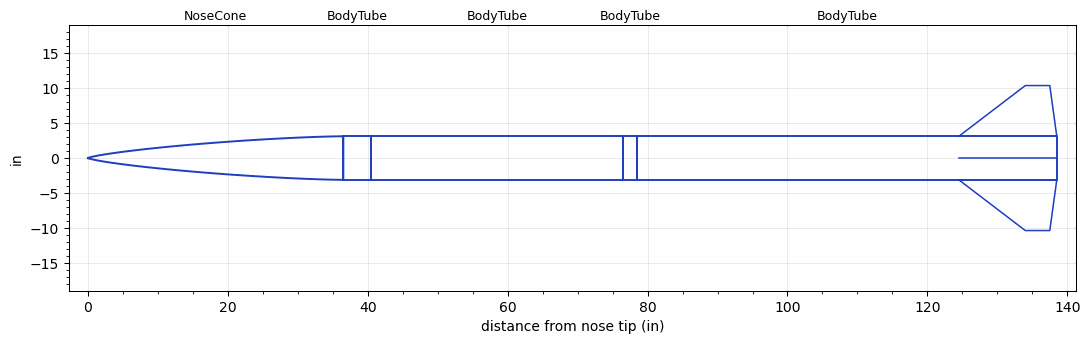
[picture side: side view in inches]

<RASAeroDocument>
 <FileVersion>2</FileVersion>
 <RocketDesign>
  <NoseCone>
   <Length>36.5</Length>
   <Diameter>6.23</Diameter>
   <Shape>Von Karman Ogive</Shape>
   <BluntRadius>0.075</BluntRadius>
   <Location>0</Location>
  </NoseCone>
  <BodyTube>
   <Length>4</Length>
   <Diameter>6.23</Diameter>
   <Location>36.5</Location>
  </BodyTube>
  <BodyTube>
   <Length>36</Length>
   <Diameter>6.23</Diameter>
   <Location>40.5</Location>
  </BodyTube>
  <BodyTube>
   <Length>2</Length>
   <Diameter>6.23</Diameter>
   <Location>76.5</Location>
  </BodyTube>
  <BodyTube>
   <Length>60</Length>
   <Diameter>6.23</Diameter>
   <Location>78.5</Location>
   <Fin>
    <Count>4</Count>
    <Chord>14</Chord>
    <Span>7.25</Span>
    <SweepDistance>9.5</SweepDistance>
    <TipChord>3.5</TipChord>
    <Thickness>0.375</Thickness>
    <LERadius>0.075</LERadius>
    <Location>14</Location>
    <AirfoilSection>Hexagonal</AirfoilSection>
    <FX1>1</FX1>
    <FX3>1</FX3>
   </Fin>
  </BodyTube>
  <Surface>Smooth Paint</Surface>
  <ModifiedBarrowman>False</ModifiedBarrowman>
  <Turbulence>False</Turbulence>
  <UseBooster1>False</UseBooster1>
  <UseBooster2>False</UseBooster2>
  <Comments>Includes new fin geometry to remove tip rake angle to allow for more accurate RasAero simluation verification</Comments>
 </RocketDesign>
 <LaunchSite>
  <Altitude>4596</Altitude>
  <Pressure>25.28</Pressure>
  <RodAngle>4</RodAngle>
  <RodLength>17</RodLength>
  <Temperature>95</Temperature>
  <WindSpeed>7</WindSpeed>
 </LaunchSite>
 <Recovery>
  <Altitude1>1500</Altitude1>
  <Altitude2>1500</Altitude2>
  <DeviceType1>Parachute</DeviceType1>
  <DeviceType2>Parachute</DeviceType2>
  <Event1>True</Event1>
  <Event2>True</Event2>
  <Size1>119.9998</Size1>
  <Size2>24</Size2>
  <EventType1>Altitude</EventType1>
  <EventType2>Altitude</EventType2>
  <CD1>1.16</CD1>
  <CD2>0</CD2>
 </Recovery>
 <SimulationList>
  <Simulation>
   <SustainerEngine>O4176  (EX)</SustainerEngine>
   <SustainerLaunchWt>139</SustainerLaunchWt>
   <SustainerNozzleDiameter>2</SustainerNozzleDiameter>
   <SustainerCG>95.03</SustainerCG>
   <SustainerIgnitionDelay>0</SustainerIgnitionDelay>
   <Booster1SeparationDelay>0</Booster1SeparationDelay>
   <Booster1IgnitionDelay>0</Booster1IgnitionDelay>
   <IncludeBooster1>False</IncludeBooster1>
   <Booster2Delay>0</Booster2Delay>
   <IncludeBooster2>False</IncludeBooster2>
   <TimetoApogee>51.82731</TimetoApogee>
   <MaxAltitude>41473.37</MaxAltitude>
   <MaxVelocity>1918.314</MaxVelocity>
  </Simulation>
  <Simulation>
   <SustainerLaunchWt>138.5684</SustainerLaunchWt>
   <SustainerCG>94.979</SustainerCG>
   <SustainerIgnitionDelay>0</SustainerIgnitionDelay>
   <Booster1SeparationDelay>0</Booster1SeparationDelay>
   <Booster1IgnitionDelay>0</Booster1IgnitionDelay>
   <IncludeBooster1>False</IncludeBooster1>
   <Booster2Delay>0</Booster2Delay>
   <IncludeBooster2>False</IncludeBooster2>
  </Simulation>
  <Simulation>
   <SustainerLaunchWt>138.5684</SustainerLaunchWt>
   <SustainerCG>94.979</SustainerCG>
   <SustainerIgnitionDelay>0</SustainerIgnitionDelay>
   <Booster1SeparationDelay>0</Booster1SeparationDelay>
   <Booster1IgnitionDelay>0</Booster1IgnitionDelay>
   <IncludeBooster1>False</IncludeBooster1>
   <Booster2Delay>0</Booster2Delay>
   <IncludeBooster2>False</IncludeBooster2>
  </Simulation>
 </SimulationList>
</RASAeroDocument>
